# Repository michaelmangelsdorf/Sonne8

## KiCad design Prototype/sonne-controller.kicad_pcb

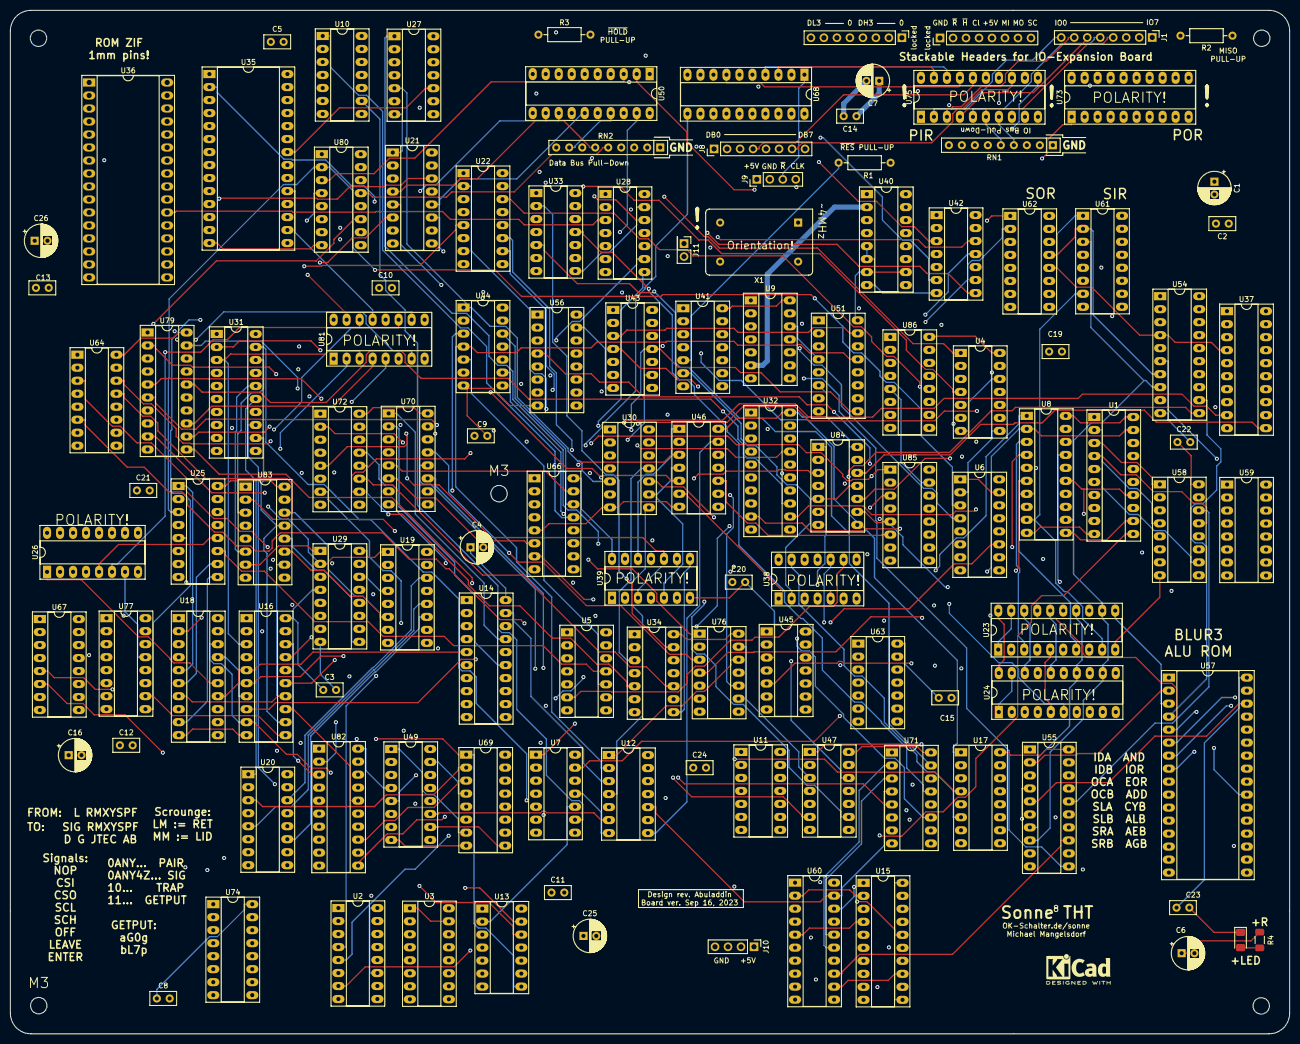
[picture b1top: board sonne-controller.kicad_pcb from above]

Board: 4 copper layers, 250.0 x 200.0 mm, 120 parts (0 on the bottom side), 344 nets.

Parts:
C1, C4, C6, C7, C16, C25, C26: C_Polarized_Small; CP_Radial_D6.3mm_P2.50mm
C2, C3, C5, C8, C9, C10, C11, C12, C13, C14, C15, C19, C20, C21, C22, C23, C24: C_Small; C_Disc_D5.0mm_W2.5mm_P2.50mm
D1: LED; LED_1206_3216Metric_Pad1.42x1.75mm_HandSolder
J1, J8: Conn_01x08_Male; PinHeader_1x08_P2.54mm_Vertical
J9, J10: Conn_01x04_Male; PinHeader_1x04_P2.54mm_Vertical
J11: Conn_02x01; PinHeader_2x01_P2.54mm_Vertical
R1, R2, R3: R7.5k; R_Axial_DIN0207_L6.3mm_D2.5mm_P10.16mm_Horizontal
R4: 500k; R_1206_3216Metric_Pad1.30x1.75mm_HandSolder
RN1, RN2: R_Network08 100K; R_Array_SIP9
U1: 74HC573; DIP-20_W7.62mm_Socket_LongPads
U2, U3, U19, U20, U25, U26, U29, U49: 74HC193; DIP-16_W7.62mm_Socket_LongPads
U4, U28, U38, U42, U46: 74HC32; DIP-14_W7.62mm_Socket_LongPads
U5: 74HC00; DIP-14_W7.62mm_Socket_LongPads
U6, U21, U22, U56, U64, U67, U74, U77: 74HC253; DIP-16_W7.62mm_Socket_LongPads
U7, U11, U45: 74HC74; DIP-14_W7.62mm_Socket_LongPads
U8, U14, U15, U16, U23, U24, U31, U32: 74AHC244; DIP-20_W7.62mm_Socket_LongPads
U9, U34, U47: 74AHC08; DIP-14_W7.62mm_Socket_LongPads
U10, U12: 74HC11; DIP-14_W7.62mm_Socket_LongPads
U13, U30, U33, U41, U43, U76: 74AHC04; DIP-14_W7.62mm_Socket_LongPads
U17: 74HC139; DIP-16_W7.62mm_Socket_LongPads
U18, U37, U50, U54, U55, U60, U68, U79, U82: 74AHC273; DIP-20_W7.62mm_Socket_LongPads
U27, U84: 74AHC02; DIP-14_W7.62mm_Socket_LongPads
U35: KM62256CLP; DIP-28_W15.24mm_Socket_LongPads
U36: SST39SF040; DIP-32_W15.24mm_Socket_LongPads
U39: 4075; DIP-14_W7.62mm_Socket_LongPads
U40: 74HC163; DIP-16_W7.62mm_Socket_LongPads
U44: 74AHC00; DIP-14_W7.62mm_Socket_LongPads
U51, U72, U85, U86: 74HC238; DIP-16_W7.62mm_Socket_LongPads
U57: 27C080; DIP-32_W15.24mm_Socket_LongPads
U58, U59: 74HC283; DIP-16_W7.62mm_Socket_LongPads
U61: 74HC595; DIP-16_W7.62mm_Socket_LongPads
U62: 74HC165; DIP-16_W7.62mm_Socket_LongPads
U63: 4078; DIP-14_W7.62mm_Socket_LongPads
U66, U70, U71: 74AHC138; DIP-16_W7.62mm_Socket_LongPads
U69, U80, U81, U83: 74HC157; DIP-16_W7.62mm_Socket_LongPads
U73, U75: 74AHC574; DIP-20_W7.62mm_Socket_LongPads
X1: CXO_DIP14; Oscillator_DIP-14
locked: Conn_01x08_Male; PinHeader_1x08_P2.54mm_Vertical
locked#2: Conn_01x08_Male; PinHeader_1x08_P2.54mm_Vertical

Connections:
+5V: C1.1, C2.1, C3.1, C4.1, C5.1, C6.1, C7.1, C8.1, C9.1, C10.1, C11.1, C12.1, C13.1, C14.1, C15.1, C16.1, C19.1, C20.1, C21.1, C22.1, C23.1, C24.1, C25.1, C26.1, J9.1, J10.1, J10.2, R1.1, R2.1, R3.1, R4.2, U1.20 (VCC), U2.11 (~LOAD), U2.16 (VCC), U3.11 (~LOAD), U3.16 (VCC), U4.14 (VCC), U5.14 (VCC), U6.16 (VCC), U7.2 (D), U7.12 (D), U7.14 (VCC), U8.20 (VCC), U9.14 (VCC), U10.4, U10.10, U10.14 (VCC), U11.2 (D), U11.12 (D), U11.14 (VCC), U12.14 (VCC), U13.14 (VCC), U14.20 (VCC), U15.11 (2A3), U15.20 (VCC), U16.20 (VCC), U17.13 (A1), U17.14 (A0), U17.15 (E), U17.16 (VCC), U18.20 (VCC), U19.4 (DOWN), U19.16 (VCC), U20.4 (DOWN), U20.16 (VCC), U21.16 (VCC), U22.16 (VCC), U23.20 (VCC), U24.20 (VCC), U25.4 (DOWN), U25.16 (VCC), U26.4 (DOWN), U26.16 (VCC), U27.14 (VCC), U28.14 (VCC), U29.4 (DOWN), U29.16 (VCC), U30.14 (VCC), U31.20 (VCC), U32.20 (VCC), U33.14 (VCC), U34.14 (VCC), U35.28 (VCC), U36.31 (PGM), U36.32 (VCC), U37.20 (VCC), U38.14 (VCC), U39.14 (VDD), U40.7 (CEP), U40.9 (~PE), U40.10 (CET), U40.16 (VCC), U41.14 (VCC), U42.14 (VCC), U43.14 (VCC), U44.14 (VCC), U45.2 (D), U45.12 (D), U45.14 (VCC), U46.14 (VCC), U47.14 (VCC), U49.4 (DOWN), U49.16 (VCC), U50.20 (VCC), U51.6 (G1), U51.16 (VCC), U54.20 (VCC), U55.20 (VCC), U56.16 (VCC), U57.32 (VCC), U58.16 (VCC), U59.16 (VCC), U60.20 (VCC), U61.16 (VCC), U62.16 (VCC), U63.14 (Vdd), U64.16 (VCC), U66.16 (VCC), U67.16 (VCC), U68.20 (VCC), U69.16 (VCC), U70.16 (VCC), U71.16 (VCC), U72.16 (VCC), U73.20 (VCC), U74.16 (VCC), U75.20 (VCC), U76.14 (VCC), U77.16 (VCC), U79.20 (VCC), U80.16 (VCC), U81.16 (VCC), U82.20 (VCC), U83.16 (VCC), U84.14 (VCC), U85.16 (VCC), U86.16 (VCC), X1.1 (EN), X1.14 (Vcc), locked.5
/A0: U24.2 (1A0), U37.2 (Q0), U56.6 (I0a), U57.12 (A0)
/A1: U24.4 (1A1), U37.5 (Q1), U56.10 (I0b), U57.11 (A1)
/A2: U24.6 (1A2), U37.6 (Q2), U57.10 (A2), U64.6 (I0a)
/A3: U24.8 (1A3), U37.9 (Q3), U57.9 (A3), U64.10 (I0b)
/A4: U24.17 (2A0), U37.12 (Q4), U57.8 (A4), U67.6 (I0a)
/A5: U24.15 (2A1), U37.15 (Q5), U57.7 (A5), U67.10 (I0b)
/A6: U24.13 (2A2), U37.16 (Q6), U57.6 (A6), U74.6 (I0a)
/A7: U24.11 (2A3), U37.19 (Q7), U57.5 (A7), U74.10 (I0b)
/ADH0: U6.7 (Za), U35.3 (A7), U36.5 (A7)
/ADH1: U6.9 (Zb), U35.25 (A8), U36.27 (A8)
/ADH2: U22.7 (Za), U35.24 (A9), U36.26 (A9)
/ADH3: U22.9 (Zb), U35.21 (A10), U36.23 (A10)
/ADH4: U21.7 (Za), U35.23 (A11), U36.25 (A11)
/ADH5: U21.9 (Zb), U35.2 (A12), U36.4 (A12)
/ADH6: U35.26 (A13), U36.28 (A13), U77.7 (Za)
/ADH7: U28.2, U77.9 (Zb)
/ADL0: U35.10 (A0), U36.12 (A0), U56.7 (Za)
/ADL1: U35.9 (A1), U36.11 (A1), U56.9 (Zb)
/ADL2: U35.8 (A2), U36.10 (A2), U64.7 (Za)
/ADL3: U35.7 (A3), U36.9 (A3), U64.9 (Zb)
/ADL4: U35.6 (A4), U36.8 (A4), U67.7 (Za)
/ADL5: U35.5 (A5), U36.7 (A5), U67.9 (Zb)
/ADL6: U33.1, U35.4 (A6), U36.6 (A6), U47.13, U74.7 (Za)
/ADL7: U10.3, U28.1, U34.12, U35.1 (A14), U47.12, U74.9 (Zb)
/ADMIT: U1.11 (Load), U7.5 (Q)
/B0: U23.2 (1A0), U54.2 (Q0), U56.5 (I1a), U57.27 (A8)
/B1: U23.4 (1A1), U54.5 (Q1), U56.11 (I1b), U57.26 (A9)
/B2: U23.6 (1A2), U54.6 (Q2), U57.23 (A10), U64.5 (I1a)
/B3: U23.8 (1A3), U54.9 (Q3), U57.25 (A11), U64.11 (I1b)
/B4: U23.17 (2A0), U54.12 (Q4), U57.4 (A12), U67.5 (I1a)
/B5: U23.15 (2A1), U54.15 (Q5), U57.28 (A13), U67.11 (I1b)
/B6: U23.13 (2A2), U54.16 (Q6), U57.29 (A14), U74.5 (I1a)
/B7: U23.11 (2A3), U54.19 (Q7), U57.3 (A15), U74.11 (I1b)
/BANKS_0: U4.6, U6.14 (A0), U21.14 (A0), U22.14 (A0), U77.14 (A0)
/BANKS_1: U4.8, U6.2 (A1), U13.13, U21.2 (A1), U22.2 (A1), U77.2 (A1)
/CLOSE: U5.12, U9.12, U27.6, U40.11 (Q3), U51.4 (~G2A), U84.2, U84.6, locked.4
/CSI: U61.11 (SRCLK), U61.12 (RCLK), U76.2
/CSO: U62.2 (CP), U76.4
/DB0: J8.1, RN2.2 (R1), U8.18 (1Y0), U14.18 (1Y0), U16.18 (1Y0), U18.3 (D0), U23.18 (1Y0), U24.18 (1Y0), U31.18 (1Y0), U32.18 (1Y0), U35.11 (Q0), U36.13 (D0), U37.3 (D0), U50.3 (D0), U54.3 (D0), U55.3 (D0), U60.3 (D0), U61.15 (QA), U62.11 (D0), U68.3 (D0), U73.2 (D0), U75.19 (Q0), U80.3 (I1a), U82.3 (D0), U83.3 (I1a)
/DB1: J8.2, RN2.3 (R2), U8.16 (1Y1), U14.16 (1Y1), U16.16 (1Y1), U18.4 (D1), U23.16 (1Y1), U24.16 (1Y1), U31.16 (1Y1), U32.16 (1Y1), U35.12 (Q1), U36.14 (D1), U37.4 (D1), U50.4 (D1), U54.4 (D1), U55.4 (D1), U60.4 (D1), U61.1 (QB), U62.12 (D1), U68.4 (D1), U73.3 (D1), U75.18 (Q1), U80.6 (I1b), U82.4 (D1), U83.6 (I1b)
/DB2: J8.3, RN2.4 (R3), U8.14 (1Y2), U14.14 (1Y2), U16.14 (1Y2), U18.7 (D2), U23.14 (1Y2), U24.14 (1Y2), U31.14 (1Y2), U32.14 (1Y2), U35.13 (Q2), U36.15 (D2), U37.7 (D2), U50.7 (D2), U54.7 (D2), U55.7 (D2), U60.7 (D2), U61.2 (QC), U62.13 (D2), U68.7 (D2), U73.4 (D2), U75.17 (Q2), U80.10 (I1c), U82.7 (D2), U83.10 (I1c)
/DB3: J8.4, RN2.5 (R4), U8.12 (1Y3), U14.12 (1Y3), U16.12 (1Y3), U18.8 (D3), U23.12 (1Y3), U24.12 (1Y3), U31.12 (1Y3), U32.12 (1Y3), U35.15 (Q3), U36.17 (D3), U37.8 (D3), U50.8 (D3), U54.8 (D3), U55.8 (D3), U60.8 (D3), U61.3 (QD), U62.14 (D3), U68.8 (D3), U73.5 (D3), U75.16 (Q3), U80.13 (I1d), U82.8 (D3), U83.13 (I1d)
/DB4: J8.5, RN2.6 (R5), U8.3 (2Y0), U14.3 (2Y0), U16.3 (2Y0), U18.13 (D4), U23.3 (2Y0), U24.3 (2Y0), U31.3 (2Y0), U32.3 (2Y0), U35.16 (Q4), U36.18 (D4), U37.13 (D4), U50.13 (D4), U54.13 (D4), U55.13 (D4), U60.13 (D4), U61.4 (QE), U62.3 (D4), U68.13 (D4), U69.3 (I1a), U73.6 (D4), U75.15 (Q4), U81.3 (I1a), U82.13 (D4)
/DB5: J8.6, RN2.7 (R6), U8.5 (2Y1), U14.5 (2Y1), U16.5 (2Y1), U18.14 (D5), U23.5 (2Y1), U24.5 (2Y1), U31.5 (2Y1), U32.5 (2Y1), U35.17 (Q5), U36.19 (D5), U37.14 (D5), U50.14 (D5), U54.14 (D5), U55.14 (D5), U60.14 (D5), U61.5 (QF), U62.4 (D5), U68.14 (D5), U69.6 (I1b), U73.7 (D5), U75.14 (Q5), U81.6 (I1b), U82.14 (D5)
/DB6: J8.7, RN2.8 (R7), U8.7 (2Y2), U14.7 (2Y2), U16.7 (2Y2), U18.17 (D6), U23.7 (2Y2), U24.7 (2Y2), U31.7 (2Y2), U32.7 (2Y2), U35.18 (Q6), U36.20 (D6), U37.17 (D6), U50.17 (D6), U54.17 (D6), U55.17 (D6), U60.17 (D6), U61.6 (QG), U62.5 (D6), U68.17 (D6), U69.10 (I1c), U73.8 (D6), U75.13 (Q6), U81.10 (I1c), U82.17 (D6)
/DB7: J8.8, RN2.9 (R8), U8.9 (2Y3), U14.9 (2Y3), U16.9 (2Y3), U18.18 (D7), U23.9 (2Y3), U24.9 (2Y3), U31.9 (2Y3), U32.9 (2Y3), U35.19 (Q7), U36.21 (D7), U37.18 (D7), U50.18 (D7), U54.18 (D7), U55.18 (D7), U60.18 (D7), U61.7 (QH), U62.6 (D7), U68.18 (D7), U69.13 (I1d), U73.9 (D7), U75.12 (Q7), U81.13 (I1d), U82.18 (D7)
/DH0: U68.12 (Q4), locked#2.1
/DH1: U68.15 (Q5), locked#2.2
/DH2: U68.16 (Q6), locked#2.3
/DH3: U68.19 (Q7), locked#2.4
/DL0: U68.2 (Q0), locked#2.5
/DL1: U68.5 (Q1), locked#2.6
/DL2: U68.6 (Q2), locked#2.7
/DL3: U68.9 (Q3), locked#2.8
/DPH: U5.9, U12.11, U27.5, U30.5, U40.12 (Q2), U44.1, U51.3 (A2), U71.6 (E3)
/EXIT: U18.11 (Cp), U30.11, U34.3
/FETCH: U4.2, U4.5, U4.9, U28.6, U42.1, U46.12
/FOP0: U55.2 (Q0), U57.2 (A16)
/FOP1: U55.5 (Q1), U57.30 (A17)
/FOP2: U55.6 (Q2), U57.31 (A18)
/FOP3: U55.9 (Q3), U57.1 (A19)
/FR0: U2.3 (QA), U6.5 (I1a)
/FR1: U2.2 (QB), U6.11 (I1b)
/FR2: U2.6 (QC), U22.5 (I1a)
/FR3: U2.7 (QD), U22.11 (I1b)
/FR4: U3.3 (QA), U21.5 (I1a)
/FR5: U3.2 (QB), U21.11 (I1b)
/FR6: U3.6 (QC), U77.5 (I1a)
/FR7: U3.7 (QD), U77.11 (I1b)
/G0: U6.4 (I2a), U50.2 (Q0)
/G1: U6.12 (I2b), U50.5 (Q1)
/G2: U22.4 (I2a), U50.6 (Q2)
/G3: U22.12 (I2b), U50.9 (Q3)
/G4: U21.4 (I2a), U50.12 (Q4)
/G5: U21.12 (I2b), U50.15 (Q5)
/G6: U50.16 (Q6), U77.4 (I2a)
/G7: U50.19 (Q7), U77.12 (I2b)
/GETPUT: U12.8, U43.13, U46.13
/IB0: U14.2 (1A0), U15.2 (1A0), U60.2 (Q0), U66.1 (A0), U72.1 (A0), U85.1 (A0)
/IB1: U14.4 (1A1), U15.4 (1A1), U60.5 (Q1), U66.2 (A1), U72.2 (A1), U85.2 (A1)
/IB2: U14.6 (1A2), U15.6 (1A2), U60.6 (Q2), U66.3 (A2), U72.3 (A2), U85.3 (A2)
/IB3: U14.8 (1A3), U17.2 (A0), U60.9 (Q3), U66.4 (E1), U72.6 (G1), U84.9, U85.5 (~G2B)
/IB4: U14.17 (2A0), U15.13 (2A2), U60.12 (Q4), U70.1 (A0), U71.1 (A0), U86.1 (A0)
/IB5: U14.15 (2A1), U17.3 (A1), U60.15 (Q5), U70.2 (A1), U71.2 (A1), U86.2 (A1)
/IB6: U12.9, U43.1, U60.16 (Q6), U70.3 (A2), U71.3 (A2), U86.3 (A2)
/IB7: U12.10, U39.11, U44.9, U60.19 (Q7), U71.4 (E1), U85.4 (~G2A), U86.4 (~G2A)
/IBNK0: U6.3 (I3a), U25.3 (QA), U80.2 (I0a)
/IBNK1: U6.13 (I3b), U25.2 (QB), U80.5 (I0b)
/IBNK2: U22.3 (I3a), U25.6 (QC), U80.11 (I0c)
/IBNK3: U22.13 (I3b), U25.7 (QD), U80.14 (I0d)
/IBNK4: U21.3 (I3a), U26.3 (QA), U81.2 (I0a)
/IBNK5: U21.13 (I3b), U26.2 (QB), U81.5 (I0b)
/IBNK6: U26.6 (QC), U77.3 (I3a), U81.11 (I0c)
/IBNK7: U26.7 (QD), U77.13 (I3b), U81.14 (I0d)
/IN_GLOBAL: U4.10, U34.11
/IO0: J1.8, RN1.9 (R8), U73.19 (Q0), U75.2 (D0)
/IO1: J1.7, RN1.8 (R7), U73.18 (Q1), U75.3 (D1)
/IO2: J1.6, RN1.7 (R6), U73.17 (Q2), U75.4 (D2)
/IO3: J1.5, RN1.6 (R5), U73.16 (Q3), U75.5 (D3)
/IO4: J1.4, RN1.5 (R4), U73.15 (Q4), U75.6 (D4)
/IO5: J1.3, RN1.4 (R3), U73.14 (Q5), U75.7 (D5)
/IO6: J1.2, RN1.3 (R2), U73.13 (Q6), U75.8 (D6)
/IO7: J1.1, RN1.2 (R1), U73.12 (Q7), U75.9 (D7)
/IPH: U27.4, U28.4
/JUMP: U39.3, U39.9
/LFETCH: U12.12, U84.3
/Lx: U28.5, U33.6
/Lx_pre: U12.13, U47.1, U86.15 (Y0)
/MISO: R2.2, U41.11, locked.6
/MOSI: U62.9 (Q7), locked.7
/Mx: U27.8, U33.10
/Mx_pre: U47.5, U86.13 (Y2)
/NZFLAG_F: U34.4, U63.1
/OFFS0: U55.12 (Q4), U58.5 (A1)
/OFFS1: U55.15 (Q5), U58.3 (A2)
/OFFS2: U55.16 (Q6), U58.14 (A3)
/OFFS3: U55.19 (Q7), U58.12 (A4), U59.3 (A2), U59.5 (A1), U59.12 (A4), U59.14 (A3)
/OFFS_0: U4.3, U56.14 (A0), U64.14 (A0), U67.14 (A0), U74.14 (A0)
/OFFS_1: U46.11, U56.2 (A1), U64.2 (A1), U67.2 (A1), U74.2 (A1), U76.11
/PC0: U19.3 (QA), U56.3 (I3a), U83.2 (I0a)
/PC1: U19.2 (QB), U56.13 (I3b), U83.5 (I0b)
/PC2: U19.6 (QC), U64.3 (I3a), U83.11 (I0c)
/PC3: U19.7 (QD), U64.13 (I3b), U83.14 (I0d)
/PC4: U20.3 (QA), U67.3 (I3a), U69.2 (I0a)
/PC5: U20.2 (QB), U67.13 (I3b), U69.5 (I0b)
/PC6: U20.6 (QC), U69.11 (I0c), U74.3 (I3a)
/PC7: U20.7 (QD), U69.14 (I0d), U74.13 (I3b)
/PH0: U43.3, U51.15 (Y0)
/PH1: U12.2, U44.4, U51.13 (Y2), U60.11 (Cp)
/PH3: U34.2, U43.11, U51.9 (Y6)
/Px: U33.12, U75.11 (Cp)
/R0: U6.6 (I0a), U16.2 (1A0), U82.2 (Q0)
/R1: U6.10 (I0b), U16.4 (1A1), U82.5 (Q1)
/R2: U16.6 (1A2), U22.6 (I0a), U82.6 (Q2)
/R3: U16.8 (1A3), U22.10 (I0b), U82.9 (Q3)
/R4: U16.17 (2A0), U21.6 (I0a), U82.12 (Q4)
/R5: U16.15 (2A1), U21.10 (I0b), U82.15 (Q5)
/R6: U16.13 (2A2), U77.6 (I0a), U82.16 (Q6)
/R7: U16.11 (2A3), U77.10 (I0b), U82.19 (Q7)
/RCOPY: U33.4, U66.6 (E3), U70.6 (E3)
/RES: U2.14 (CLR), U3.14 (CLR), U25.14 (CLR), U26.14 (CLR), U27.12, U29.14 (CLR), U38.2, U41.1, U41.6, U49.14 (CLR), U84.5, U84.11
/RET: U28.13, U33.8
/SCL: U27.11, U76.6
/SCLK: U45.5 (Q), locked.8
/SCROUNGE: U39.13, U42.11, U71.5 (E2)
/SIG_pre: U85.15 (Y0), U86.5 (~G2B)
/TRAP: U30.12, U38.4, U39.4
/XA0: U15.18 (1Y0), U56.4 (I2a)
/XA1: U15.16 (1Y1), U56.12 (I2b)
/XA2: U15.14 (1Y2), U64.4 (I2a)
/XA3: U15.12 (1Y3), U64.12 (I2b)
/XA4: U15.3 (2Y0), U67.4 (I2a)
/XA5: U15.5 (2Y1), U67.12 (I2b)
/XA6: U15.7 (2Y2), U74.4 (I2a)
/XA7: U15.9 (2Y3), U74.12 (I2b)
/Y0: U32.2 (1A0), U79.2 (Q0)
/Y1: U32.4 (1A1), U79.5 (Q1)
/Y2: U32.6 (1A2), U79.6 (Q2)
/Y3: U32.8 (1A3), U79.9 (Q3)
/Y4: U32.17 (2A0), U79.12 (Q4)
/Y5: U32.15 (2A1), U79.15 (Q5)
/Y6: U32.13 (2A2), U79.16 (Q6)
/Y7: U32.11 (2A3), U79.19 (Q7)
/ZFLAG_F: U34.9, U63.13
/pre_LID: U5.10, U42.13, U44.5, U47.6
/xA: U13.3, U72.9 (Y6)
/xB: U13.5, U72.7 (Y7)
/xC: U30.9, U39.5, U46.4, U72.10 (Y5)
/xD: U68.11 (Cp), U72.15 (Y0)
/xE: U34.10, U72.11 (Y4)
/xG: U50.11 (Cp), U72.14 (Y1)
/xJ: U39.1, U72.13 (Y2)
/xM_pre: U47.2, U47.4, U85.13 (Y2)
/xP: U30.4, U73.11 (Cp)
/xT: U34.5, U72.12 (Y3)
/xX: U13.8, U69.1 (S), U83.1 (S)
/xY: U13.10, U46.5, U80.1 (S), U81.1 (S)
/~ALU_HOLD: U7.1 (~R), U76.8
/~BOF: U2.13 (~BO), U3.4 (DOWN)
/~CLEAR: U11.10 (~S), U27.1
/~COF: U2.12 (~CO), U3.5 (UP)
/~CSI: U70.14 (O1), U76.1
/~CSO: U70.13 (O2), U76.3
/~DPH: U28.10, U30.6
/~ENTER: U2.4 (DOWN), U70.7 (O7)
/~EXIT: U11.4 (~S), U30.10
/~Fx: U8.1 (1OE), U8.19 (2OE), U71.7 (O7)
/~GETA: U17.4 (O0), U46.2
/~GETB: U17.6 (O2), U38.13
/~GETPUT: U17.1 (E), U43.12, U84.8
/~HOLD: U41.4, U46.9
/~IN_RAM: U30.2, U35.20 (~CS)
/~IN_ROM: U28.3, U30.1, U36.22 (CE)
/~LEAVE: U2.5 (UP), U70.9 (O6)
/~LID: U5.8, U25.5 (UP), U43.9
/~Lx: U33.5, U71.15 (O0)
/~MEMOE: U27.10, U35.22 (~OE), U36.24 (OE)
/~Mx: U33.11, U71.13 (O2)
/~OFF: U9.9, U70.10 (O5)
/~PH0: U11.1 (~R), U11.13 (~R), U43.4, U46.10, U60.1 (~Mr), U85.6 (G1), U86.6 (G1)
/~PH3: U38.12, U39.12, U42.5, U42.9, U43.10, U46.1
/~POE: U45.9 (Q), U73.1 (OE)
/~PUTA: U17.5 (O1), U24.1 (1OE), U24.19 (2OE), U42.4
/~PUTB: U17.7 (O3), U23.1 (1OE), U23.19 (2OE), U42.10
/~Px: U33.13, U71.9 (O6), U75.1 (OE)
/~RCOPY: U33.3, U39.10, U72.5 (~G2B)
/~RES: J9.3, U9.10, U18.1 (~Mr), U37.1 (~Mr), U41.2, U47.10, U50.1 (~Mr), U54.1 (~Mr), U55.1 (~Mr), U61.10 (~SRCLR), U68.1 (~Mr), U79.1 (~Mr), U82.1 (~Mr)
/~RET: U9.1, U19.11 (~LOAD), U20.11 (~LOAD), U33.9, U44.3
/~Rx: U16.1 (1OE), U16.19 (2OE), U71.14 (O1)
/~SCH: U45.4 (~S), U70.11 (O4)
/~SCL: U70.12 (O3), U76.5
/~SIG: U66.15 (O0), U70.5 (E2)
/~Sx: U61.13 (~OE), U71.10 (O5)
/~TRAP: U12.3, U14.1 (1OE), U14.19 (2OE), U28.8, U30.13
/~XXx: U31.1 (1OE), U31.19 (2OE), U71.12 (O3)
/~Yx: U9.2, U71.11 (O4)
/~xA: U5.2, U13.4
/~xB: U5.4, U13.6
/~xC: U12.4, U30.8
/~xF: U43.5, U47.9, U66.7 (O7)
/~xM: U10.1, U66.13 (O2)
/~xP: U30.3, U45.13 (~R), U66.9 (O6)
/~xR: U44.12, U44.13, U66.14 (O1)
/~xS: U62.1 (~PL), U66.10 (O5)
/~xX: U12.5, U13.9, U66.12 (O3)
/~xY: U13.11, U66.11 (O4)
GND: C1.2, C2.2, C3.2, C4.2, C5.2, C6.2, C7.2, C8.2, C9.2, C10.2, C11.2, C12.2, C13.2, C14.2, C15.2, C16.2, C19.2, C20.2, C21.2, C22.2, C23.2, C24.2, C25.2, C26.2, D1.1 (K), J9.2, J10.3, J10.4, RN1.1 (common), RN2.1 (common), U1.1 (OE), U1.10 (GND), U2.1 (B), U2.8 (GND), U2.9 (D), U2.10 (C), U2.15 (A), U3.1 (B), U3.8 (GND), U3.9 (D), U3.10 (C), U3.15 (A), U4.7 (GND), U4.12, U4.13, U5.7 (GND), U6.1 (OEa), U6.8 (GND), U6.15 (OEb), U7.3 (C), U7.7 (GND), U7.11 (C), U8.10 (GND), U9.7 (GND), U10.7 (GND), U11.3 (C), U11.7 (GND), U11.11 (C), U12.7 (GND), U13.7 (GND), U14.10 (GND), U14.11 (2A3), U14.13 (2A2), U15.1 (1OE), U15.8 (1A3), U15.10 (GND), U15.15 (2A1), U15.17 (2A0), U15.19 (2OE), U16.10 (GND), U17.8 (GND), U18.10 (GND), U19.8 (GND), U20.8 (GND), U21.1 (OEa), U21.8 (GND), U21.15 (OEb), U22.1 (OEa), U22.8 (GND), U22.15 (OEb), U23.10 (GND), U24.10 (GND), U25.8 (GND), U26.8 (GND), U27.7 (GND), U28.7 (GND), U29.8 (GND), U30.7 (GND), U31.10 (GND), U32.10 (GND), U33.7 (GND), U34.7 (GND), U35.14 (GND), U36.1 (A18), U36.2 (A16), U36.3 (A15), U36.16 (GND), U36.29 (A14), U36.30 (A17), U37.10 (GND), U38.7 (GND), U39.7 (VSS), U40.3 (D0), U40.4 (D1), U40.5 (D2), U40.6 (D3), U40.8 (GND), U41.7 (GND), U42.7 (GND), U43.7 (GND), U44.7 (GND), U45.3 (C), U45.7 (GND), U45.11 (C), U46.7 (GND), U47.7 (GND), U49.8 (GND), U50.10 (GND), U51.5 (~G2B), U51.8 (GND), U54.10 (GND), U55.10 (GND), U56.1 (OEa), U56.8 (GND), U56.15 (OEb), U57.16 (GND), U57.22 (~CE), U57.24 (~OE), U58.7 (C0), U58.8 (GND), U59.8 (GND), U60.10 (GND), U61.8 (GND), U62.8 (GND), U62.10 (DS), U62.15 (~CE), U63.7 (Vss), U64.1 (OEa), U64.8 (GND), U64.15 (OEb), U66.5 (E2), U66.8 (GND), U67.1 (OEa), U67.8 (GND), U67.15 (OEb), U68.10 (GND), U69.8 (GND), U69.15 (E), U70.4 (E1), U70.8 (GND), U71.8 (GND), U72.4 (~G2A), U72.8 (GND), U73.10 (GND), U74.1 (OEa), U74.8 (GND), U74.15 (OEb), U75.10 (GND), U76.7 (GND), U77.1 (OEa), U77.8 (GND), U77.15 (OEb), U79.10 (GND), U80.8 (GND), U80.15 (E), U81.8 (GND), U81.15 (E), U82.10 (GND), U83.8 (GND), U83.15 (E), U84.7 (GND), U85.8 (GND), U86.8 (GND), X1.7 (GND), locked.1
unnamed: D1.2 (A), R4.1
unnamed: R1.2, U41.5, locked.2
unnamed: R3.2, U41.9, locked.3
unnamed: J9.4, J11.1
unnamed: J11.2, U9.5, X1.8 (OUT)
unnamed: U1.2 (D0), U58.4 (S1)
unnamed: U1.3 (D1), U58.1 (S2)
unnamed: U1.4 (D2), U58.13 (S3)
unnamed: U1.5 (D3), U58.10 (S4)
unnamed: U1.6 (D4), U59.4 (S1)
unnamed: U1.7 (D5), U59.1 (S2)
unnamed: U1.8 (D6), U59.13 (S3)
unnamed: U1.9 (D7), U59.10 (S4)
unnamed: U1.19 (Q0), U8.2 (1A0), U63.2
unnamed: U1.18 (Q1), U8.4 (1A1), U63.3
unnamed: U1.17 (Q2), U8.6 (1A2), U63.4
unnamed: U1.16 (Q3), U8.8 (1A3), U63.5
unnamed: U1.15 (Q4), U8.17 (2A0), U63.9
unnamed: U1.14 (Q5), U8.15 (2A1), U63.10
unnamed: U1.13 (Q6), U8.13 (2A2), U63.11
unnamed: U1.12 (Q7), U8.11 (2A3), U63.12
unnamed: U7.4 (~S), U47.8
unnamed: U7.9 (Q), U10.9
unnamed: U7.13 (~R), U84.13
unnamed: U7.10 (~S), U13.2
unnamed: U10.2, U42.6
unnamed: U10.5, U13.12
unnamed: U4.4, U10.6
unnamed: U4.1, U10.8
unnamed: U10.11, U76.10
unnamed: U10.13, U42.8
unnamed: U5.13, U11.5 (Q)
unnamed: U9.13, U11.9 (Q)
unnamed: U12.1, U76.12
unnamed: U18.2 (Q0), U25.15 (A)
unnamed: U18.5 (Q1), U25.1 (B)
unnamed: U18.6 (Q2), U25.10 (C)
unnamed: U18.9 (Q3), U25.9 (D)
unnamed: U18.12 (Q4), U26.15 (A)
unnamed: U18.15 (Q5), U26.1 (B)
unnamed: U18.16 (Q6), U26.10 (C)
unnamed: U18.19 (Q7), U26.9 (D)
unnamed: U19.15 (A), U29.3 (QA), U31.2 (1A0)
unnamed: U19.1 (B), U29.2 (QB), U31.4 (1A1)
unnamed: U19.10 (C), U29.6 (QC), U31.6 (1A2)
unnamed: U19.14 (CLR), U20.14 (CLR), U38.3
unnamed: U19.9 (D), U29.7 (QD), U31.8 (1A3)
unnamed: U19.5 (UP), U84.1
unnamed: U19.12 (~CO), U20.5 (UP)
unnamed: U20.15 (A), U31.17 (2A0), U49.3 (QA)
unnamed: U20.1 (B), U31.15 (2A1), U49.2 (QB)
unnamed: U20.10 (C), U31.13 (2A2), U49.6 (QC)
unnamed: U20.9 (D), U31.11 (2A3), U49.7 (QD)
unnamed: U25.12 (~CO), U26.5 (UP)
unnamed: U5.11, U25.11 (~LOAD), U26.11 (~LOAD)
unnamed: U27.2, U43.8
unnamed: U27.3, U28.12, U39.6
unnamed: U27.9, U42.3
unnamed: U28.9, U44.8
unnamed: U28.11, U34.1
unnamed: U29.15 (A), U83.4 (Za)
unnamed: U29.1 (B), U83.7 (Zb)
unnamed: U29.10 (C), U83.9 (Zc)
unnamed: U29.9 (D), U83.12 (Zd)
unnamed: U29.5 (UP), U44.6
unnamed: U29.12 (~CO), U49.5 (UP)
unnamed: U12.6, U29.11 (~LOAD), U49.11 (~LOAD)
unnamed: U9.3, U32.1 (1OE), U32.19 (2OE)
unnamed: U33.2, U34.13
unnamed: U34.6, U39.2
unnamed: U34.8, U39.8
unnamed: U10.12, U35.27 (~WE)
unnamed: U5.3, U37.11 (Cp), U38.10, U84.12
unnamed: U9.11, U38.1
unnamed: U38.5, U46.6
unnamed: U38.8, U76.9
unnamed: U5.5, U38.11
unnamed: U9.6, U40.2 (CP)
unnamed: U40.14 (Q0), U51.1 (A0)
unnamed: U40.13 (Q1), U51.2 (A1)
unnamed: U40.1 (~MR), U84.4
unnamed: U41.3, U41.8
unnamed: U41.10, U41.13
unnamed: U42.2, U84.10
unnamed: U42.12, U44.2, U47.3, U76.13
unnamed: U43.2, U44.10
unnamed: U27.13, U45.1 (~R)
unnamed: U9.8, U45.10 (~S)
unnamed: U5.1, U46.3
unnamed: U9.4, U46.8
unnamed: U49.15 (A), U69.4 (Za)
unnamed: U49.1 (B), U69.7 (Zb)
unnamed: U49.10 (C), U69.9 (Zc)
unnamed: U49.9 (D), U69.12 (Zd)
unnamed: U5.6, U13.1, U38.9, U54.11 (Cp)
unnamed: U43.6, U55.11 (Cp)
unnamed: U57.13 (D0), U58.6 (B1)
unnamed: U57.14 (D1), U58.2 (B2)
unnamed: U57.15 (D2), U58.15 (B3)
unnamed: U57.17 (D3), U58.11 (B4)
unnamed: U57.18 (D4), U59.6 (B1)
unnamed: U57.19 (D5), U59.2 (B2)
unnamed: U57.20 (D6), U59.15 (B3)
unnamed: U57.21 (D7), U59.11 (B4)
unnamed: U58.9 (C4), U59.7 (C0)
unnamed: U41.12, U61.14 (SER)
unnamed: U38.6, U79.11 (Cp)
unnamed: U79.3 (D0), U80.4 (Za)
unnamed: U79.4 (D1), U80.7 (Zb)
unnamed: U79.7 (D2), U80.9 (Zc)
unnamed: U79.8 (D3), U80.12 (Zd)
unnamed: U79.13 (D4), U81.4 (Za)
unnamed: U79.14 (D5), U81.7 (Zb)
unnamed: U79.17 (D6), U81.9 (Zc)
unnamed: U79.18 (D7), U81.12 (Zd)
unnamed: U44.11, U82.11 (Cp)
